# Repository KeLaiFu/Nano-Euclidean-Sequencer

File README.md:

# Nano-Euclidean-Sequencer
Eurorack adaption of an original kosmo module by instructables.com/member/ljbrackney. Current code is operational but needs some fine tuning.   

Current Status:
Hardware - finished.
Software - almost finished.

NOTE! If anyone wants to build this, please post a pull request or whatever they are here and I will dig up the latest firmware.

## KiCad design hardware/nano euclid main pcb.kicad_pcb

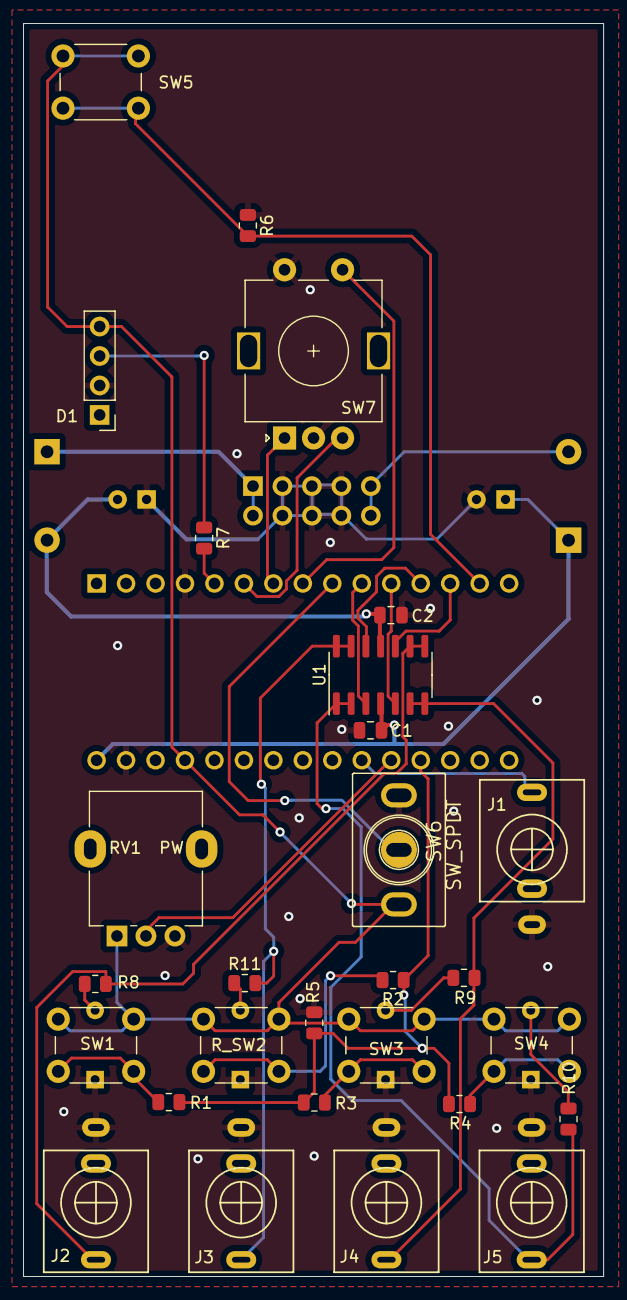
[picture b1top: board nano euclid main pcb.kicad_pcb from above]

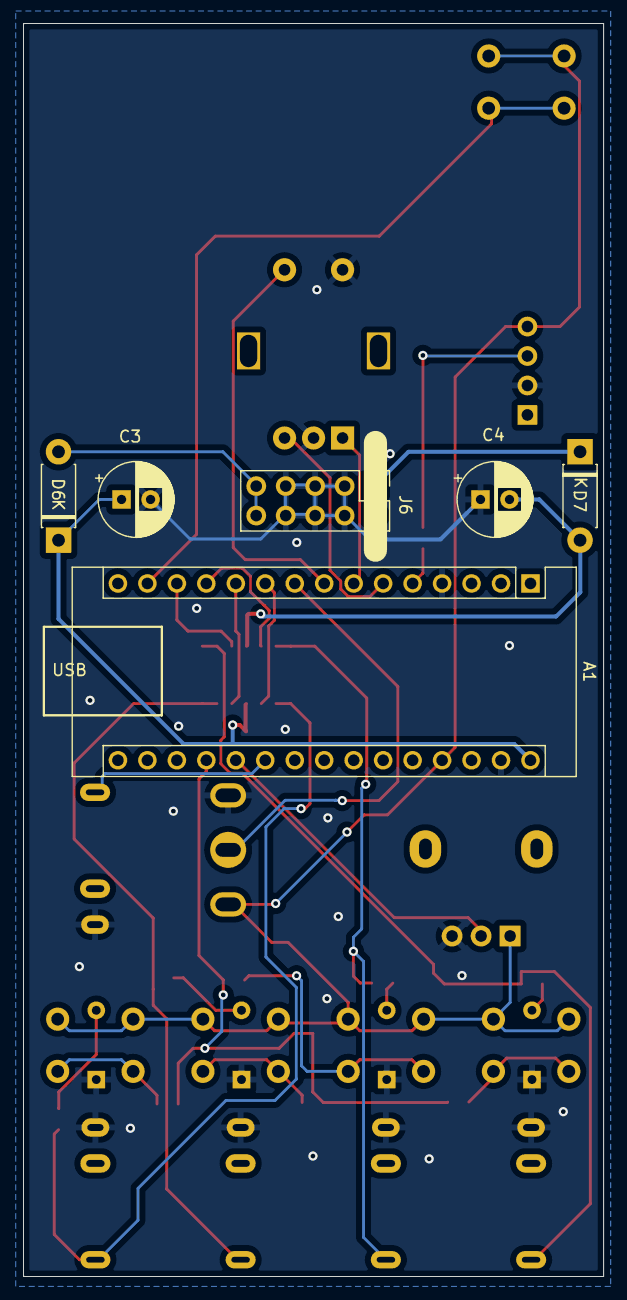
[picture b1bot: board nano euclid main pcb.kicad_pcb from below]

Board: 2 copper layers, 50.0 x 108.0 mm, 34 parts (6 on the bottom side), 32 nets.

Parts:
A1: Arduino_Nano_v3.x; Arduino_Nano
C1, C2: 0.1uF; C_0805_2012Metric
C3, C4: 10uF; CP_Radial_D6.3mm_P2.50mm
D1: NeoPixel_THT; PinHeader_1x04_P2.54mm_Vertical
D6, D7: 1N5817; D_DO-41_SOD81_P7.62mm_Horizontal
J1: CLOCK; PJ398SM
J2, J3, J4, J5: AudioJack2_Ground; PJ398SM
J6: Synth_power_2x5; PinHeader_2x05_P2.54mm_Vertical
R1, R2, R3, R4, R5, R6, R7, R8, R9, R10, R11: R; R_0805_2012Metric
RV1  PW: R_Potentiometer; Potentiometer_Alpha_RD901F-40-00D_Single_Vertical
R_SW2: SW_Push; SW_PUSH_LED_6mm
SW1, SW3, SW4: SW_Push; SW_PUSH_LED_6mm
SW5: SW_Push; SW_PUSH_6mm
SW6: SW_SPDT; SPDT_KIT
SW7: RotaryEncoder_Switch; RotaryEncoder_Alps_EC11E-Switch_Vertical_H20mm
U1: TL074; SOIC-14_3.9x8.7mm_P1.27mm

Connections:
+12V: A1.30 (VIN), C1.1, C3.1, D6.1 (K), U1.4 (V+)
-12V: C2.1, C4.2, D7.2 (A), U1.11 (V-)
GND: A1.4 (GND), A1.29 (GND), C1.2, C2.2, C3.2, C4.1, D1.2 (GND), J1.S, J2.S, J3.S, J4.S, J5.S, J6.3 (GND), J6.4 (GND), J6.5 (GND), J6.6 (GND), J6.7 (GND), J6.8 (GND), R5.2, R6.1, RV1 PW.3, R_SW2.4 (K), SW1.4 (K), SW3.4 (K), SW4.4 (K), SW6.1 (A), SW7.C, SW7.S2
unnamed: A1.5 (D2), R7.2
unnamed: A1.6 (D3), SW7.B
unnamed: A1.7 (D4), SW7.A
unnamed: A1.8 (D5), SW7.S1
unnamed: A1.9 (D6), SW6.2 (B)
unnamed: A1.10 (D7), U1.3 (+)
unnamed: A1.11 (D8), U1.5 (+)
unnamed: A1.12 (D9), U1.12 (+)
unnamed: A1.13 (D10), U1.10 (+)
unnamed: A1.14 (D11), R6.2, SW5.2
unnamed: A1.19 (A0), R1.1, R2.1, R3.1, R4.1, R5.1
unnamed: A1.20 (A1), RV1 PW.2
unnamed: A1.21 (A2), J1.T
unnamed: A1.27 (+5V), D1.4 (DIN), RV1 PW.1, R_SW2.1, SW1.1, SW3.1, SW4.1, SW5.1, SW6.3 (C)
unnamed: D1.3 (VDD), R7.1
unnamed: D6.2 (A), J6.9 (+12V), J6.10 (+12V)
unnamed: D7.1 (K), J6.1 (-12V), J6.2 (-12V)
unnamed: J2.T, R8.1, U1.8, U1.9 (-)
unnamed: J3.T, R11.2, U1.13 (-), U1.14
unnamed: J4.T, R9.2, U1.6 (-), U1.7
unnamed: J5.T, R10.2, U1.1, U1.2 (-)
unnamed: R1.2, SW1.2
unnamed: R2.2, R_SW2.2
unnamed: R3.2, SW3.2
unnamed: R4.2, SW4.2
unnamed: R8.2, SW1.3 (A)
unnamed: R9.1, SW3.3 (A)
unnamed: R10.1, SW4.3 (A)
unnamed: R11.1, R_SW2.3 (A)

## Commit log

2022-04-06 Create 1
2026-05-23 Add contributor note about firmware availability
    Added a note for contributors regarding firmware.
